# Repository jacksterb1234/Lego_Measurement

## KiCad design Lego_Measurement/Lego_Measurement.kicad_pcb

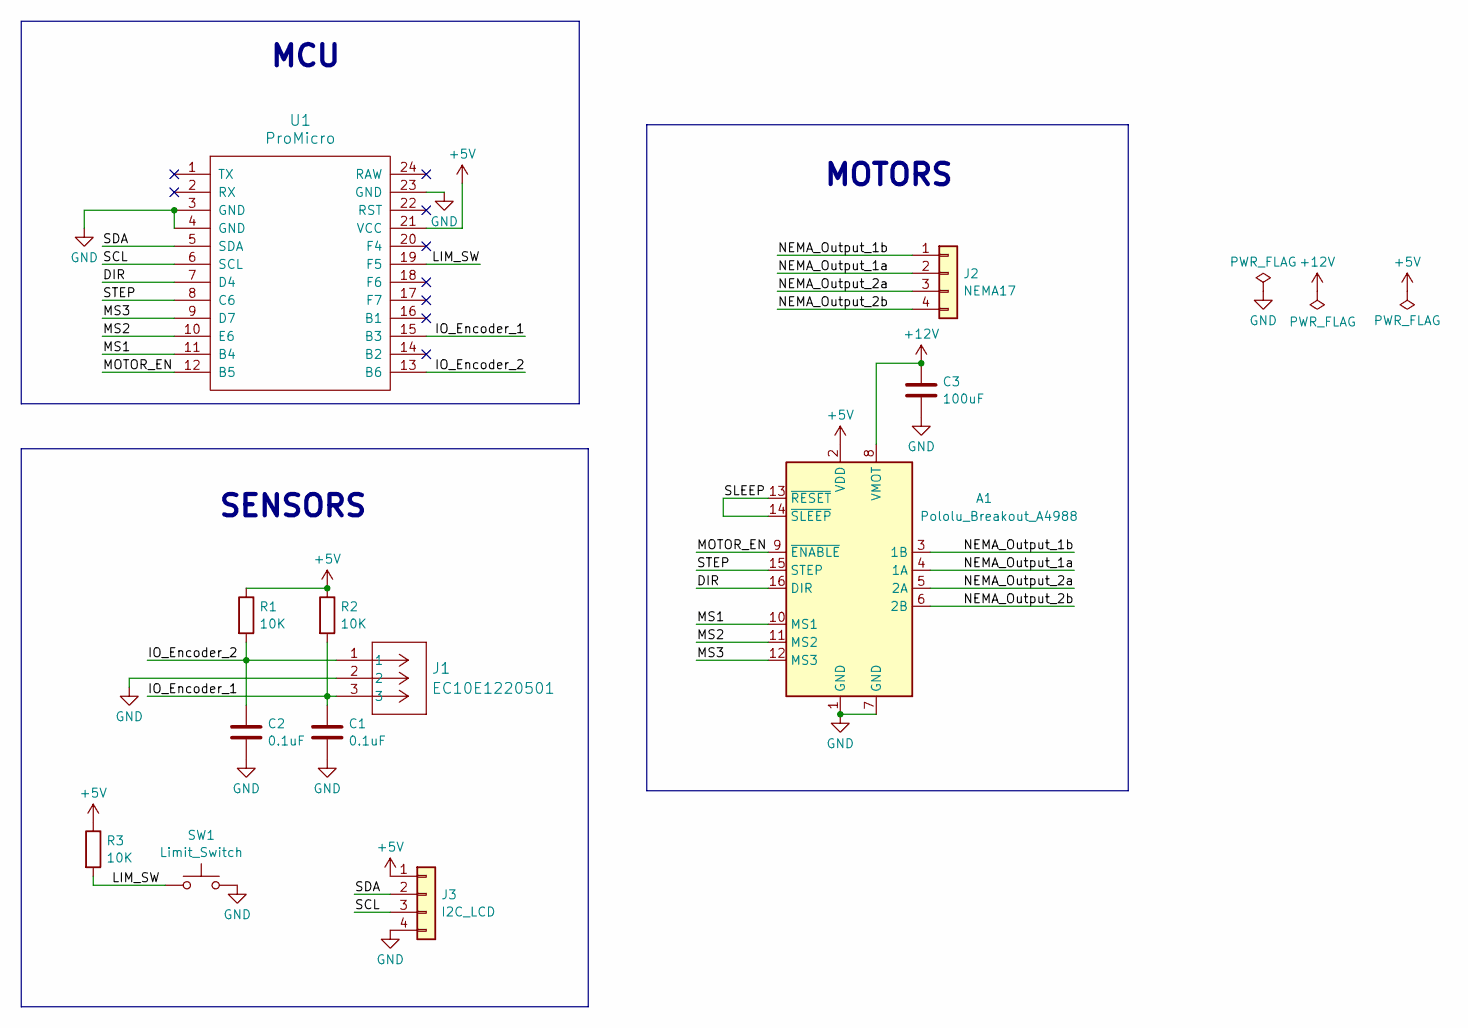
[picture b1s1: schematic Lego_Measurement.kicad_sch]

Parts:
A1: Pololu_Breakout_A4988; Pololu_Breakout-16_15.2x20.3mm
C1, C2: 0.1uF; C_Disc_D5.0mm_W2.5mm_P2.50mm
C3: 100uF; C_Radial_D8.0mm_H11.5mm_P3.50mm
J1: EC10E1220501; CONN03_EC10E_9P8X6P1_ALPS
J2: NEMA17; PinHeader_1x04_P2.54mm_Vertical
J3: I2C_LCD; PinHeader_1x04_P2.54mm_Vertical
R1, R2, R3: 10K; R_Axial_DIN0207_L6.3mm_D2.5mm_P7.62mm_Horizontal
SW1: Limit_Switch; PinHeader_2x01_P2.54mm_Vertical
U1: ProMicro; ProMicro-EnforcedTop

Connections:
+5V: A1.2 (VDD), J3.1, R1.1, R2.1, R3.1, U1.21 (VCC)
+12V: A1.8 (VMOT), C3.1
/DIR: A1.16 (DIR), U1.7 (D4)
/IO_Encoder_1: C1.1, J1.3, R2.2, U1.15 (B3)
/IO_Encoder_2: C2.1, J1.1, R1.2, U1.13 (B6)
/LIM_SW: R3.2, SW1.1, U1.19 (F5)
/MOTOR_EN: A1.9 (~ENABLE), U1.12 (B5)
/MS1: A1.10 (MS1), U1.11 (B4)
/MS2: A1.11 (MS2), U1.10 (E6)
/MS3: A1.12 (MS3), U1.9 (D7)
/NEMA_Output_1a: A1.4 (1A), J2.2
/NEMA_Output_1b: A1.3 (1B), J2.1
/NEMA_Output_2a: A1.5 (2A), J2.3
/NEMA_Output_2b: A1.6 (2B), J2.4
/SCL: J3.3, U1.6 (SCL)
/SDA: J3.2, U1.5 (SDA)
/SLEEP: A1.13 (~RESET), A1.14 (~SLEEP)
/STEP: A1.15 (STEP), U1.8 (C6)
GND: A1.1 (GND), A1.7 (GND), C1.2, C2.2, C3.2, J1.2, J3.4, SW1.2, U1.3 (GND), U1.4 (GND), U1.23 (GND)

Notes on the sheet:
MOTORS
MCU
SENSORS

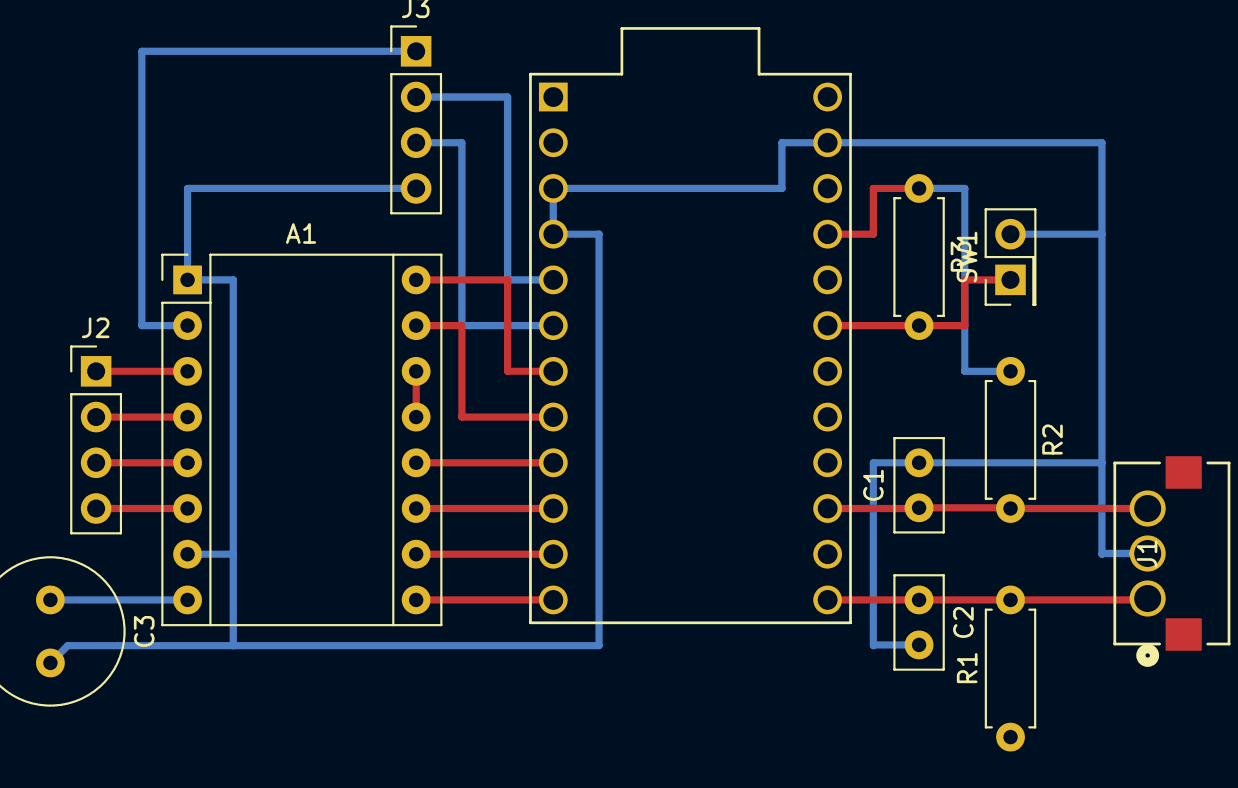
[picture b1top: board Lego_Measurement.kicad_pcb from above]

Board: 4 copper layers, 12 parts (0 on the bottom side), 19 nets.
